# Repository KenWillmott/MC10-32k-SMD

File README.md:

MC10-32k-SMD

For more details, consult the wiki: https://github.com/KenWillmott/MC10-32k-SMD/wiki

A 32k memory upgrade PCB for the Radio Shack MC-10 microcomputer. It replaces the two 2kb RAM chips and the bodged 74LS32 in the MC-10. The minimal install gives you contiguous memory from 0x0000 to 0x7FFF (except for the CPU registers in low memory). So stock Micro Color Basic recognizes and uses the the upper 16k of that, and the lower half is available for general or machine language use. There are two options:
1. Page select inputs: board inputs L0 and L1 can be connected to any digital outputs, then they will select one of four video page addresses as follows:
   
2. Battery backup: when U4 DS1210 is installed, and 3.0V is provided at the EXT BATT terminals, the memory becomes non-volatile (contents remain while main power is removed)

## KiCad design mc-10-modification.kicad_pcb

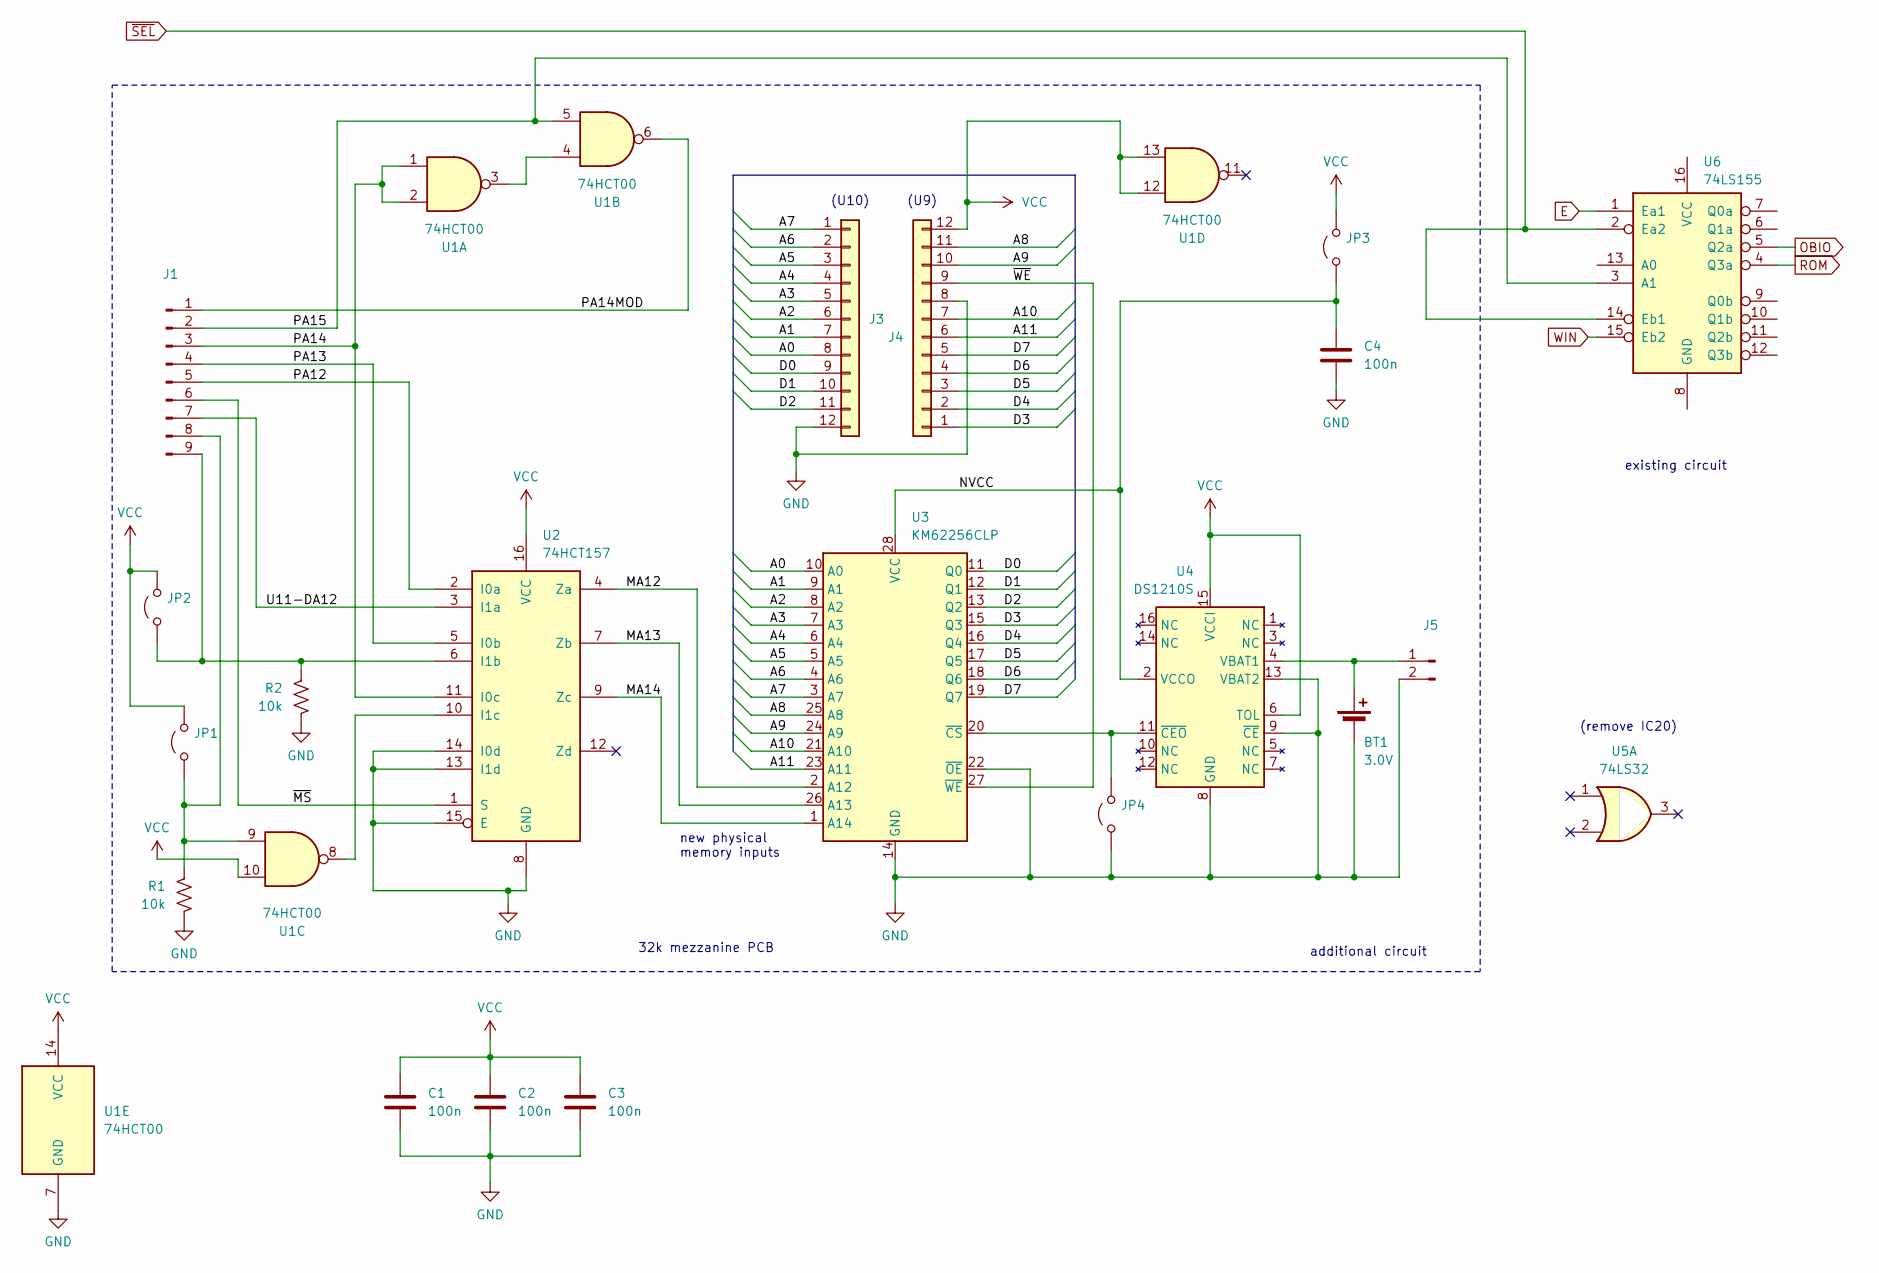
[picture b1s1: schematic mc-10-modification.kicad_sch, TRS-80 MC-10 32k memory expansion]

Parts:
BT1: 3.0V; BatteryHolder_Keystone_500
C1, C2, C3, C4: 100n; C_0603_1608Metric
J1: Conn_01x09_Pin; PinHeader_1x09_P2.54mm_Vertical
J3, J4: Conn_01x12; PinHeader_1x12_P2.54mm_Vertical
J5: Conn_01x02_Pin; PinHeader_1x02_P2.54mm_Vertical
JP1, JP2, JP3, JP4: Jumper_2_Open; SolderJumper-2_P1.3mm_Open_RoundedPad1.0x1.5mm
R1, R2: 10k; R_0603_1608Metric
U1: 74HCT00; SO-14_3.9x8.65mm_P1.27mm
U2: 74HCT157; SOP-16_3.9x9.9mm_P1.27mm
U3: KM62256CLP; SOP-28_8.4x18.16mm_P1.27mm
U4: DS1210S; SOIC-16W_7.5x10.3mm_P1.27mm
U5: 74LS32
U6: 74LS155

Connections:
/A0: J3.8, U3.10 (A0)
/A1: J3.7, U3.9 (A1)
/A2: J3.6, U3.8 (A2)
/A3: J3.5, U3.7 (A3)
/A4: J3.4, U3.6 (A4)
/A5: J3.3, U3.5 (A5)
/A6: J3.2, U3.4 (A6)
/A7: J3.1, U3.3 (A7)
/A8: J4.11, U3.25 (A8)
/A9: J4.10, U3.24 (A9)
/A10: J4.7, U3.21 (A10)
/A11: J4.6, U3.23 (A11)
/D0: J3.9, U3.11 (Q0)
/D1: J3.10, U3.12 (Q1)
/D2: J3.11, U3.13 (Q2)
/D3: J4.1, U3.15 (Q3)
/D4: J4.2, U3.16 (Q4)
/D5: J4.3, U3.17 (Q5)
/D6: J4.4, U3.18 (Q6)
/D7: J4.5, U3.19 (Q7)
/MA12: U2.4 (Za), U3.2 (A12)
/MA13: U2.7 (Zb), U3.26 (A13)
/MA14: U2.9 (Zc), U3.1 (A14)
/NVCC: C4.1, JP3.1 (A), U3.28 (VCC), U4.2 (VCCO)
/PA12: J1.5, U2.2 (I0a)
/PA13: J1.4, U2.5 (I0b)
/PA14: J1.3, U1.1, U1.2, U2.11 (I0c)
/PA14MOD: J1.1, U1.6
/PA15: J1.2, U1.5, U6.3 (A1)
/U11-DA12: J1.7, U2.3 (I1a)
/~MS: J1.6, U2.1 (S)
/~WE: J4.9, U3.27 (~WE)
GND: BT1.2 (-), C1.2, C2.2, C3.2, C4.2, J3.12, J4.8, J5.2, JP4.1 (A), R1.2, R2.2, U1.7 (GND), U2.8 (GND), U2.13 (I1d), U2.14 (I0d), U2.15 (E), U3.14 (GND), U3.22 (~OE), U4.8 (GND), U4.9 (~CE), U4.13 (VBAT2)
unnamed: BT1.1 (+), J5.1, U4.4 (VBAT1)
unnamed: J1.8, JP1.1 (A), R1.1, U1.9
unnamed: J1.9, JP2.1 (A), R2.1, U2.6 (I1b)
unnamed: JP4.2 (B), U3.20 (~CS), U4.11 (~CEO)
unnamed: U1.3, U1.4
unnamed: U1.8, U2.10 (I1c)
unnamed: U6.2 (Ea2), U6.14 (Eb1)
VCC: C1.1, C2.1, C3.1, J4.12, JP1.2 (B), JP2.2 (B), JP3.2 (B), U1.10, U1.12, U1.13, U1.14 (VCC), U2.16 (VCC), U4.6 (TOL), U4.15 (VCCI)

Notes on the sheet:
32k mezzanine PCB
(remove IC20)
(U9)
additional circuit
(U10)
existing circuit
new physical memory inputs

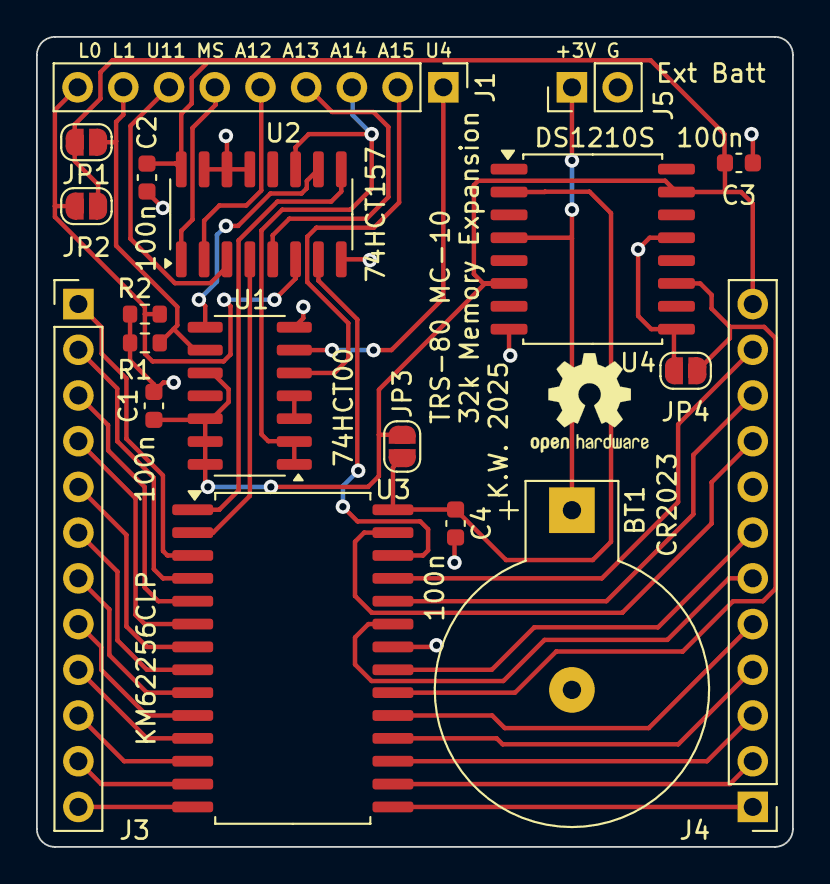
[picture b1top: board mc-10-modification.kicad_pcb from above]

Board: 2 copper layers, 42.0 x 45.0 mm, 19 parts (0 on the bottom side), 40 nets.

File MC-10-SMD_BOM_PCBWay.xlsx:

|  |  | xxxx xxxx xxxxx xxPCS BOM (Sample Bill of Materials)
Item # | *Designator | *Qty | Manufacturer | *Mfg Part # | Description / Value | *Package/Footprint | Type | Your Instructions / Notes
1 | U2 | 1 |  | 74HCT157 | SOP-16_3.9x9.9mm_P1.27mm | SOP-16_3.9x9.9mm_P1.27mm | SMD
2 | JP2,JP1 | 2 |  |  | SolderJumper-2_P1.3mm_Open_RoundedPad1.0x1.5mm | SolderJumper-2_P1.3mm_Open_RoundedPad1.0x1.5mm | DNS | [DNP不要贴];
3 | J4,J3 | 2 |  |  | PinHeader_1x12_P2.54mm_Vertical | PinHeader_1x12_P2.54mm_Vertical | SMD | [DNP不要贴];
4 | U3 | 1 |  | KM62256CLP | SOP-28_8.4x18.16mm_P1.27mm | SOP-28_8.4x18.16mm_P1.27mm | SMD
5 | C4,C3,C1,C2 | 4 |  | CC0603KRX7R6BB104 | 100n | C_0603_1608Metric | SMD
6 | J1 | 1 |  |  | PinHeader_1x09_P2.54mm_Vertical | PinHeader_1x09_P2.54mm_Vertical | SMD | [DNP不要贴];
7 | U4 | 1 |  | DS1210S-ND | SOIC-16W_7.5x10.3mm_P1.27mm | SOIC-16W_7.5x10.3mm_P1.27mm | SMD
8 | R2,R1 | 2 |  | RC0603FR-0710KL | 10k | R_0603_1608Metric | SMD
9 | J5 | 1 |  | Conn_01x02_Pin | PinHeader_1x02_P2.54mm_Vertical | PinHeader_1x02_P2.54mm_Vertical | SMD | [DNP不要贴];
10 | BT1 | 1 |  | BatteryHolder_Keystone_500 | BatteryHolder_Keystone_500 | BatteryHolder_Keystone_500 | DNS
11 | U1 | 1 |  | 74HCT00 | SO-14_3.9x8.65mm_P1.27mm | SO-14_3.9x8.65mm_P1.27mm | SMD
Need a quick and accurante quote? Need an efficient production? Please read SMT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
Click for Instructions on How to Create a BOM

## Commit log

2025-07-19 Delete New_Library.kicad_sym
    Didn't belong here
